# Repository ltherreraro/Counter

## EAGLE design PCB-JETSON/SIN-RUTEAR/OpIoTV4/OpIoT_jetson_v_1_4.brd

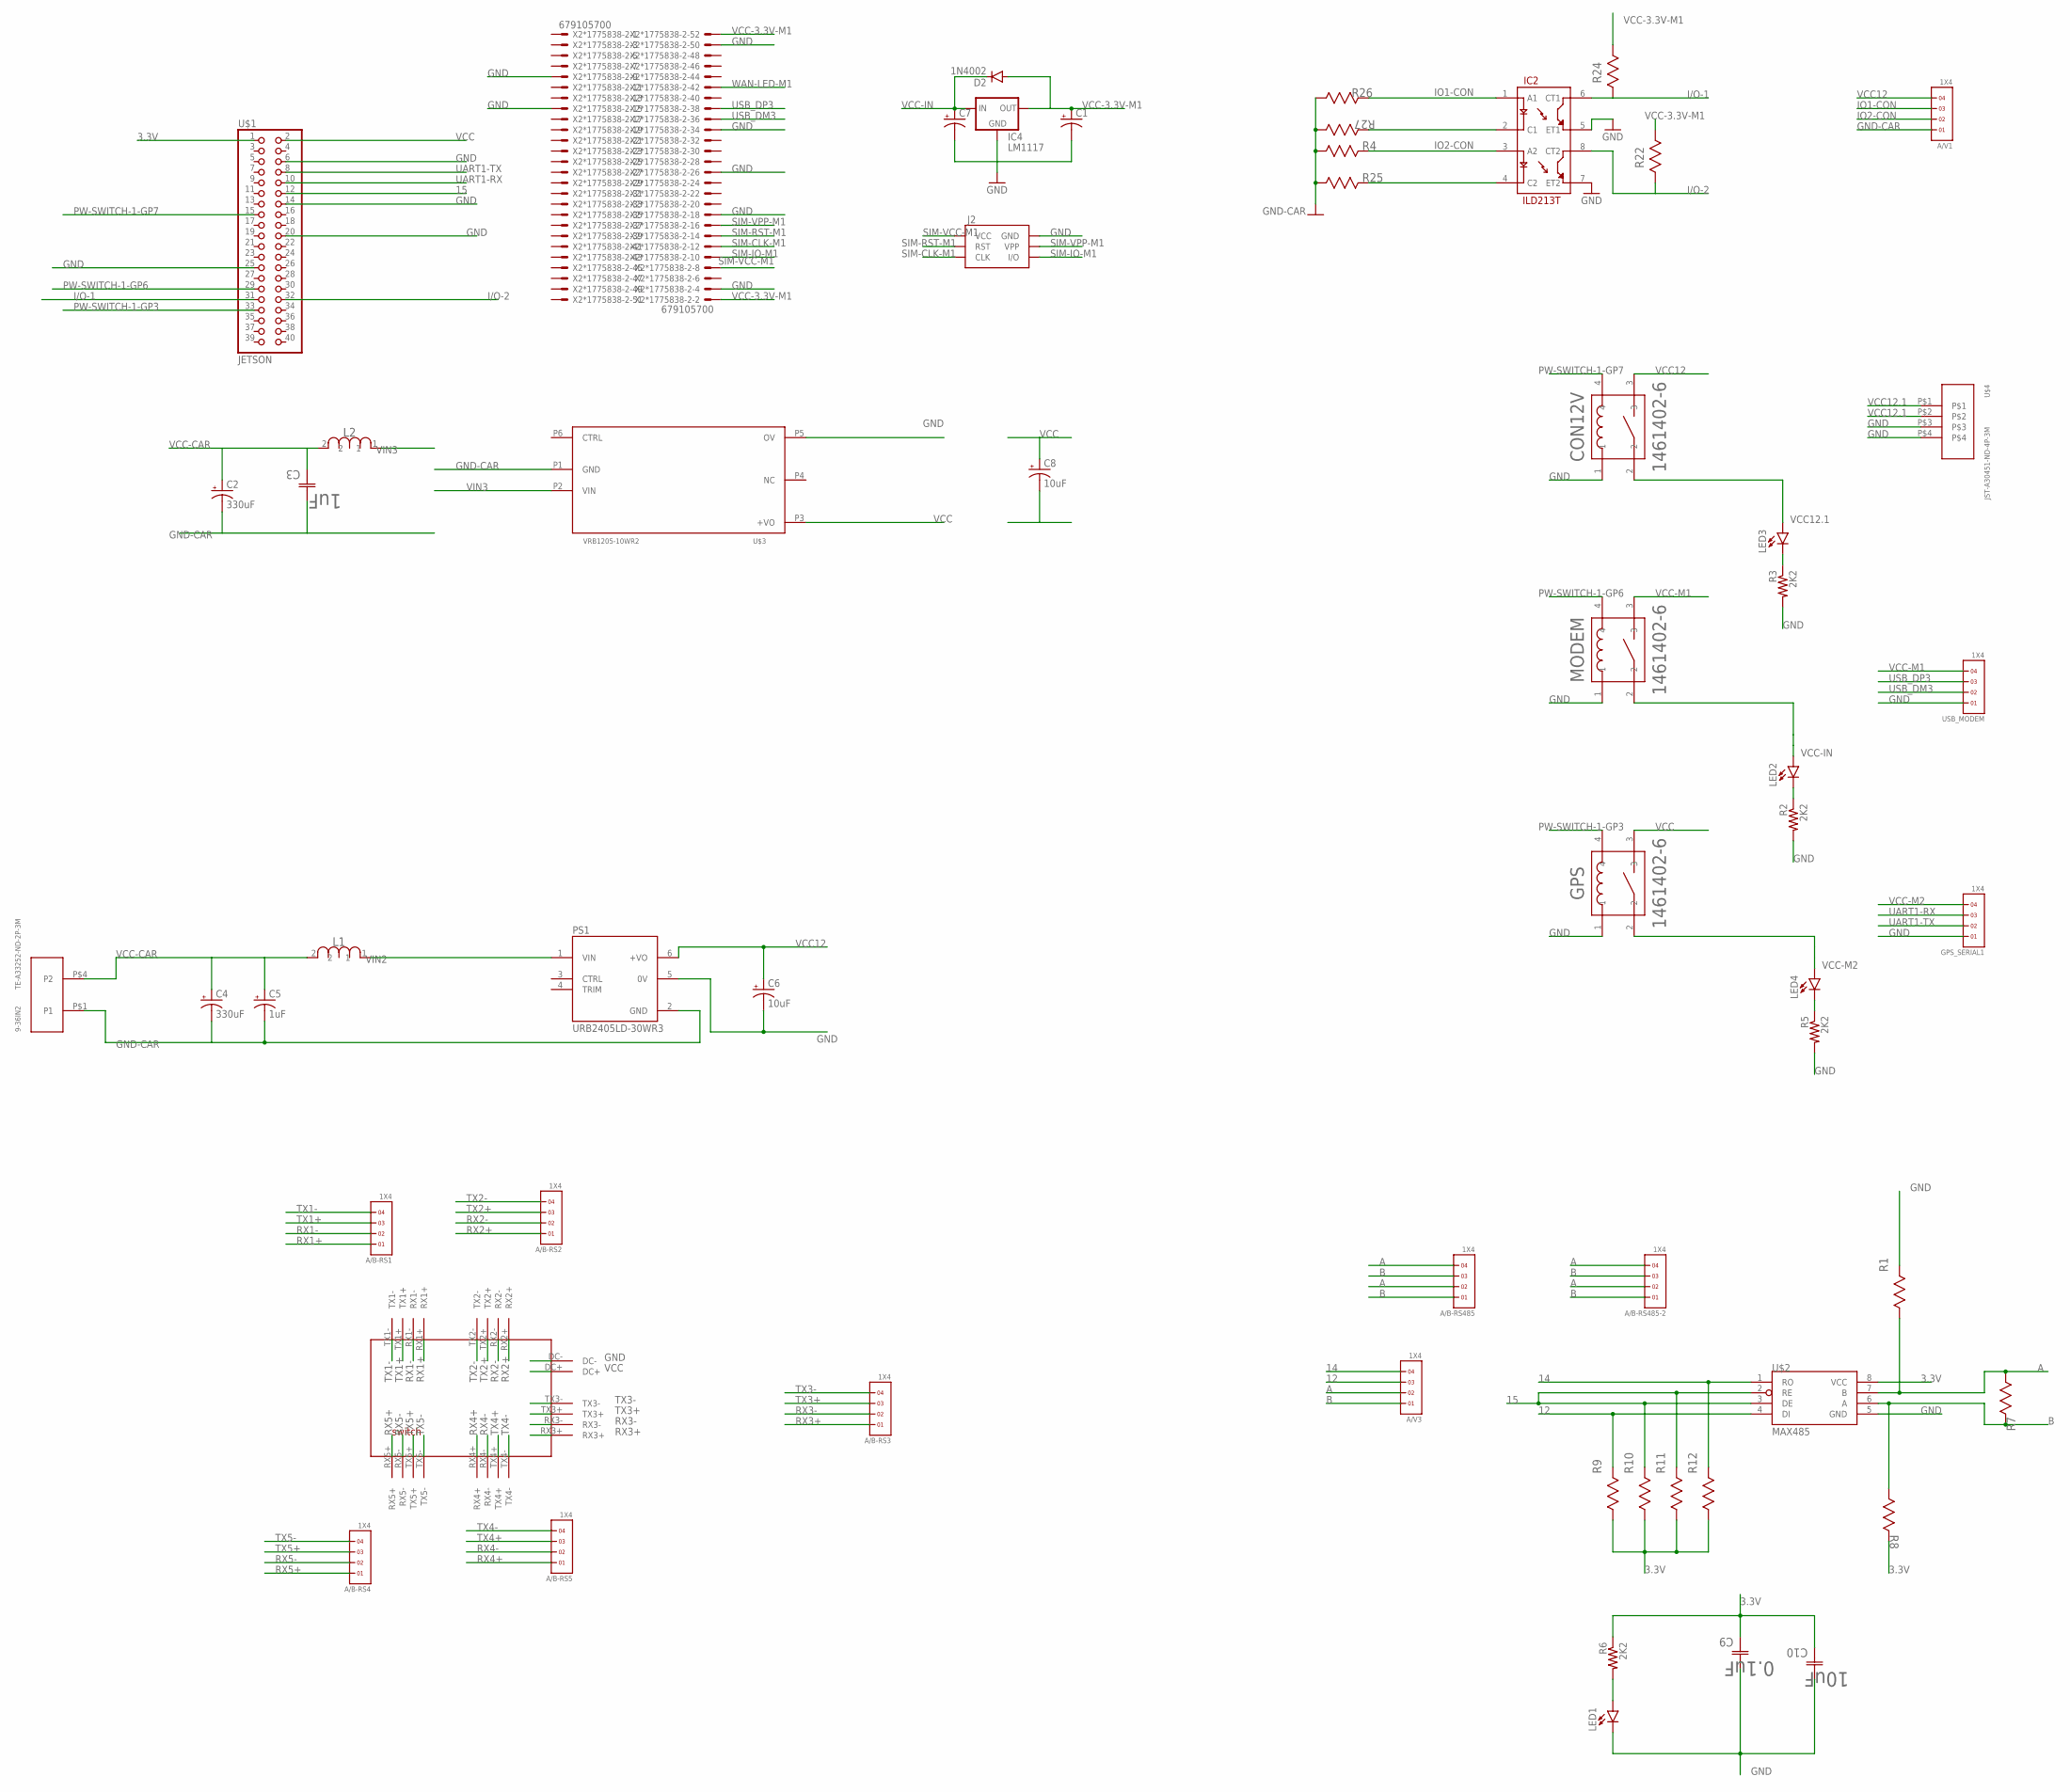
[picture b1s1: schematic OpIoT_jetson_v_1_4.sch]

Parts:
9-36IN2: TE-A33252-ND-2P-3M
A/B-RS1, A/B-RS2, A/B-RS3, A/B-RS4, A/B-RS5, A/B-RS485, A/B-RS485-2: 1X4
A/V1, A/V3: 1X4
C1, C7: CAP_POL1206-KIT; EIA3216-KIT
C2, C4: 330uF; UD-10X10_NICHICON
C3: 1uF; CAPC3216X110N
C5: 1uF; EIA3216-KIT
C6, C8: 10uF; EIA3216-KIT
C9: 0.1uF; CAPC3216X110N
C10: 10uF; CAPC3216X110N
CON12V: 1461402-6; RELAY_1461402-6
D2: 1N4002; SMA-DIODE-KIT
GPS: 1461402-6; RELAY_1461402-6
GPS_SERIAL1: 1X4
IC2: ILD213T; SO08
IC4: LM1117; SOT223
J2: SIMHOLDERSIM; SIMHOLDER
L1, L2: 4.7uH; INDC3225X22N
LED1, LED2, LED3, LED4: LEDCHIPLED_1206; CHIPLED_1206
MODEM: 1461402-6; RELAY_1461402-6
PS1: URB2405LD-30WR3; CONV_URB2405LD-30WR3
R1: 20K; RESC3216X71N
R2, R3, R5, R6: 2K2; M1206
R4, R26: 4K7; RESC3216X71N
R7: 120; RESC3216X71N
R8: 20k; RESC3216X71N
R9, R10, R11, R12: 10k; RESC3216X71N
R22, R24: 300K; RESC3216X71N
R25, R27: 2.2K; RESC3216X71N
U$1: JETSON; 2X20
U$2: MAX485; SO08
U$3: VRB1205-10WR2; MORNSUN-5V
U$4: JST-A30451-ND-4P-3M; TE-A30451-4P-TH-3M
U$6: SWITCH; JP4
USB_MODEM: 1X4
X2*1775838-2: 679105700

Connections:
3.3V: C9.2 (C2), C10.2 (C2), R6.1, R8.1 (R1), R9.2 (R2), R10.2 (R2), R11.2 (R2), R12.2 (R2), U$1.1, U$2.8 (VCC)
12: A/V3.3, R9.1 (R1), U$2.4 (DI)
14: A/V3.4, R12.1 (R1), U$2.1 (RO)
15: R10.1 (R1), R11.1 (R1), U$1.12, U$2.2 (RE), U$2.3 (DE)
A: A/B-RS485.2, A/B-RS485.4, A/B-RS485-2.2, A/B-RS485-2.4, A/V3.2, R1.2 (R2), R7.1 (R1), U$2.7 (B)
B: A/B-RS485.1, A/B-RS485.3, A/B-RS485-2.1, A/B-RS485-2.3, A/V3.1, R7.2 (R2), R8.2 (R2), U$2.6 (A)
GND: C1.C (-), C6.C (-), C7.C (-), C8.C (-), C9.1 (C1), C10.1 (C1), CON12V.1, GPS.1, GPS_SERIAL1.1, IC2.5 (ET1), IC2.7 (ET2), IC4.1 (GND), J2.C5 (GND), LED1.C, MODEM.1, PS1.5 (0V), R1.1 (R1), R2.2, R3.2, R5.2, U$1.6, U$1.14, U$1.20, U$1.25, U$2.5 (GND), U$3.P5 (OV), U$4.P$3, U$4.P$4, U$6.DC-, USB_MODEM.1, X2*1775838-2.4, X2*1775838-2.9, X2*1775838-2.15, X2*1775838-2.18, X2*1775838-2.26, X2*1775838-2.34, X2*1775838-2.50
GND-CAR: 9-36IN2.P$1 (P1), A/V1.1, C2.-, C3.1 (C1), C4.-, C5.C (-), PS1.2 (GND), R4.2 (R2), R25.1 (R1), R26.2 (R2), R27.1 (R1), U$3.P1 (GND)
I/O-1: IC2.6 (CT1), R24.2 (R2), U$1.31
I/O-2: IC2.8 (CT2), R22.2 (R2), U$1.32
IO1-CON: A/V1.3, IC2.1 (A1), R26.1 (R1)
IO2-CON: A/V1.2, IC2.3 (A2), R4.1 (R1)
unnamed: LED1.A, R6.2
unnamed: LED2.C, R2.1
unnamed: LED3.C, R3.1
unnamed: LED4.C, R5.1
unnamed: IC2.2 (C1), R27.2 (R2)
unnamed: IC2.4 (C2), R25.2 (R2)
PW-SWITCH-1-GP3: GPS.4, U$1.33
PW-SWITCH-1-GP6: MODEM.4, U$1.29
PW-SWITCH-1-GP7: CON12V.4, U$1.15
RX1+: A/B-RS1.1, U$6.RX1+
RX1-: A/B-RS1.2, U$6.RX1-
RX2+: A/B-RS2.1, U$6.RX2+
RX2-: A/B-RS2.2, U$6.RX2-
RX3+: A/B-RS3.1, U$6.RX3+
RX3-: A/B-RS3.2, U$6.RX3-
RX4+: A/B-RS5.1, U$6.RX4+
RX4-: A/B-RS5.2, U$6.RX4-
RX5+: A/B-RS4.1, U$6.RX5+
RX5-: A/B-RS4.2, U$6.RX5-
SIM-CLK-M1: J2.C3 (CLK), X2*1775838-2.12
SIM-IO-M1: J2.C7 (I/O), X2*1775838-2.10
SIM-RST-M1: J2.C2 (RST), X2*1775838-2.14
SIM-VCC-M1: J2.C1 (VCC), X2*1775838-2.8
SIM-VPP-M1: J2.C6 (VPP), X2*1775838-2.16
TX1+: A/B-RS1.3, U$6.TX1+
TX1-: A/B-RS1.4, U$6.TX1-
TX2+: A/B-RS2.3, U$6.TX2+
TX2-: A/B-RS2.4, U$6.TX2-
TX3+: A/B-RS3.3, U$6.TX3+
TX3-: A/B-RS3.4, U$6.TX3-
TX4+: A/B-RS5.3, U$6.TX4+
TX4-: A/B-RS5.4, U$6.TX4-
TX5+: A/B-RS4.3, U$6.TX5+
TX5-: A/B-RS4.4, U$6.TX5-
UART1-RX: GPS_SERIAL1.3, U$1.10
UART1-TX: GPS_SERIAL1.2, U$1.8
USB_DM3: USB_MODEM.2, X2*1775838-2.36
USB_DP3: USB_MODEM.3, X2*1775838-2.38
VCC: C8.A (+), GPS.3, U$1.2, U$3.P3 (+VO), U$6.DC+
VCC12: A/V1.4, C6.A (+), CON12V.3, PS1.6 (+VO)
VCC12.1: CON12V.2, LED3.A, U$4.P$1, U$4.P$2
VCC-3.3V-M1: C1.A (+), D2.A, IC4.2 (OUT), R22.1 (R1), R24.1 (R1), X2*1775838-2.2, X2*1775838-2.52
VCC-CAR: 9-36IN2.P$4 (P2), C2.+, C3.2 (C2), C4.+, C5.A (+), L1.2, L2.2
VCC-IN: C7.A (+), D2.C, IC4.3 (IN), LED2.A, MODEM.2
VCC-M1: MODEM.3, USB_MODEM.4
VCC-M2: GPS.2, GPS_SERIAL1.4, LED4.A
VIN2: L1.1, PS1.1 (VIN)
VIN3: L2.1, U$3.P2 (VIN)
WAN-LED-M1: X2*1775838-2.42

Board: 2 copper layers, 59 parts (2 on the bottom side), 60 nets, no tracks yet.

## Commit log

2023-11-16 archivos driver sierra
2023-11-16 instrucciones oficiales sierra
2023-11-16 comandos activacion modulos
2023-12-04 Create escucha4_7

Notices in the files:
parts and their libraries:
SparkFun-Connectors: Licensing: Creative Commons ShareAlike 4.0 International - https://creativecommons.org/licenses/by-sa/4.0
